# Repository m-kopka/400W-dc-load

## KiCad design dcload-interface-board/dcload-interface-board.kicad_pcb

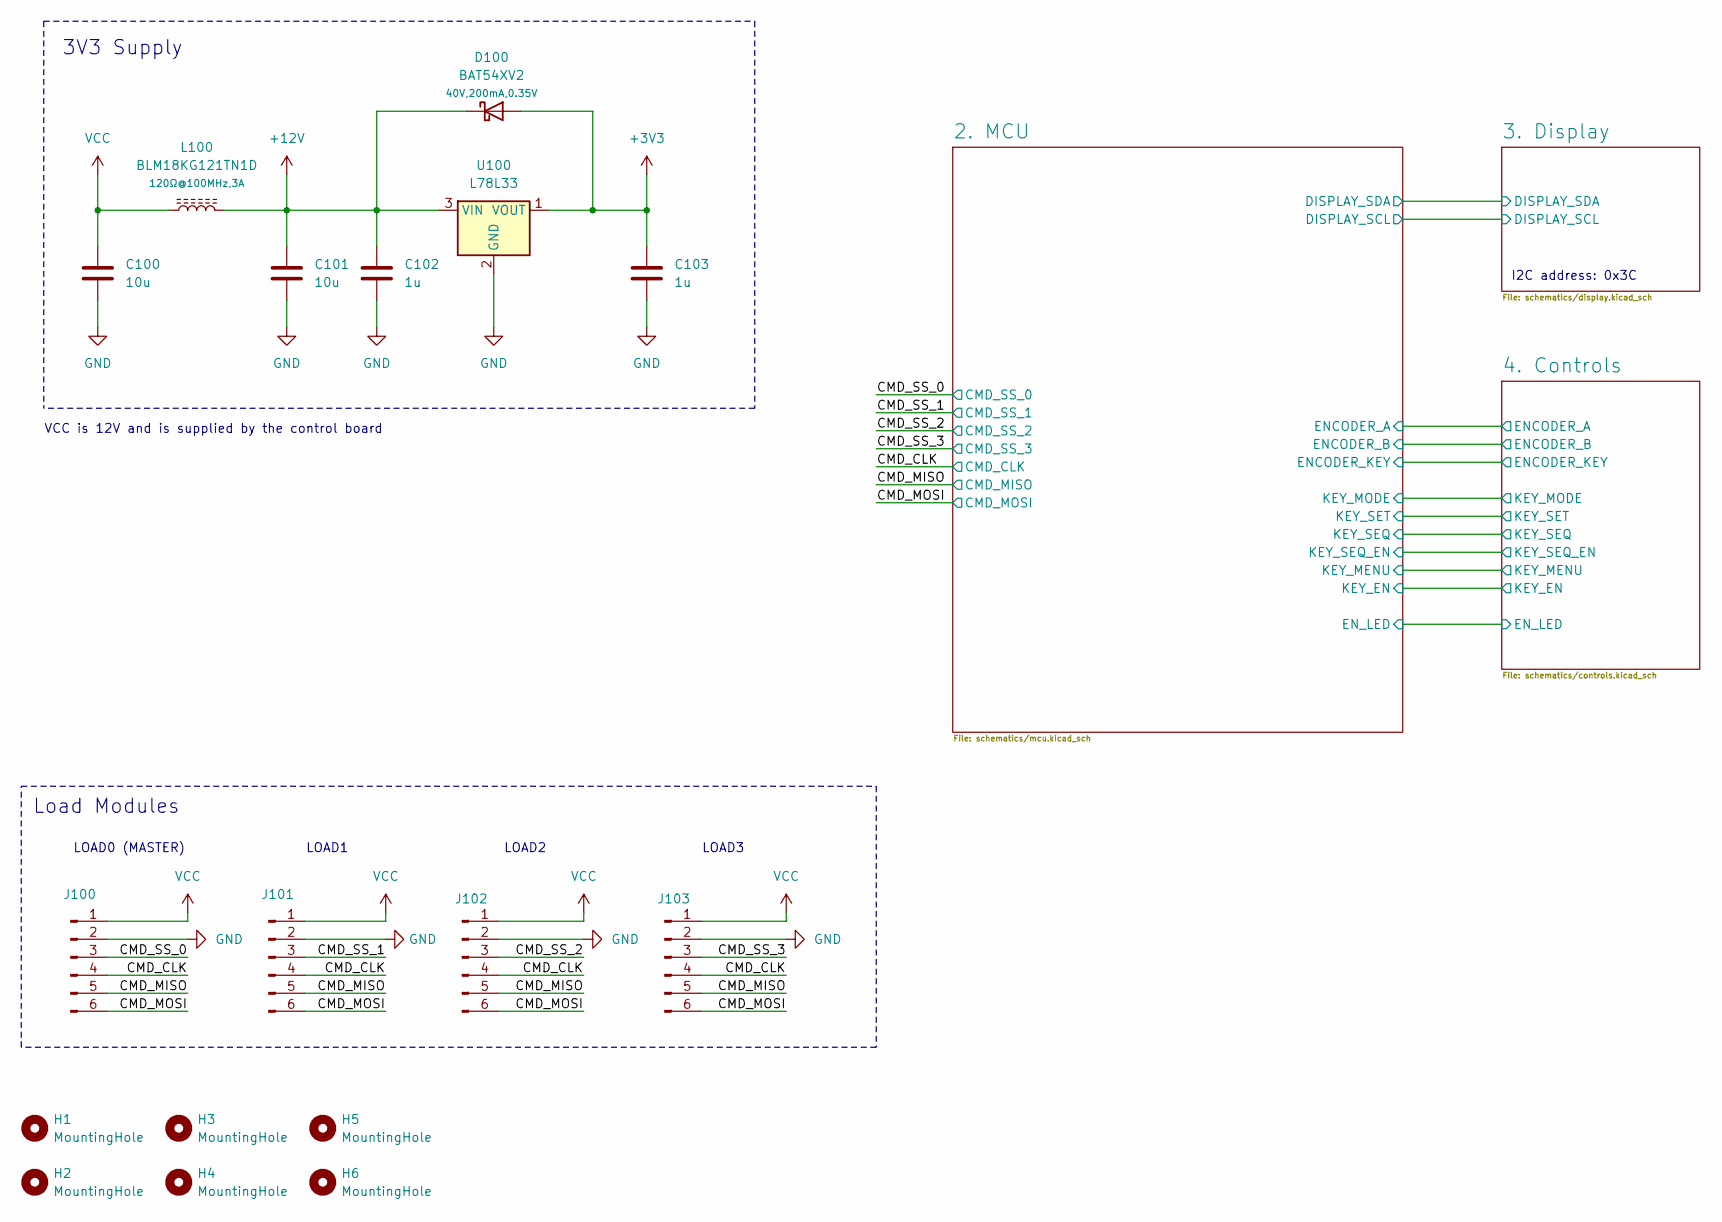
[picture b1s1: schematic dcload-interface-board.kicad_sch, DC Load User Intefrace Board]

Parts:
C100, C101: 10u; C_0603_1608Metric
C102, C103: 1u; C_0603_1608Metric
D100: BAT54XV2; SOD-523
H1, H2, H3, H4, H5, H6: MountingHole; MountingHole_3.2mm_M3
J100, J101, J102, J103: Conn_01x06_Male; PinHeader_1x06_P2.54mm_Vertical
L100: BLM18KG121TN1D; R_0603_1608Metric
U100: L78L33; SOT-89-3

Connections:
+3V3: C103.1, D100.2 (A), U100.1 (VOUT); also elsewhere on the board
+12V: C101.1, C102.1, D100.1 (K), L100.2, U100.3 (VIN)
/CMD_CLK: J100.4, J101.4, J102.4, J103.4; also elsewhere on the board
/CMD_MISO: J100.5, J101.5, J102.5, J103.5; also elsewhere on the board
/CMD_MOSI: J100.6, J101.6, J102.6, J103.6; also elsewhere on the board
/CMD_SS_0: J100.3; also elsewhere on the board
/CMD_SS_1: J101.3; also elsewhere on the board
/CMD_SS_2: J102.3; also elsewhere on the board
/CMD_SS_3: J103.3; also elsewhere on the board
GND: C100.2, C101.2, C102.2, C103.2, J100.2, J101.2, J102.2, J103.2, U100.2 (GND); also elsewhere on the board
VCC: C100.1, J100.1, J101.1, J102.1, J103.1, L100.1

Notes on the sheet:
Load Modules
LOAD1
VCC is 12V and is supplied by the control board
3V3 Supply
LOAD2
LOAD0 (MASTER)
I2C address: 0x3C
LOAD3

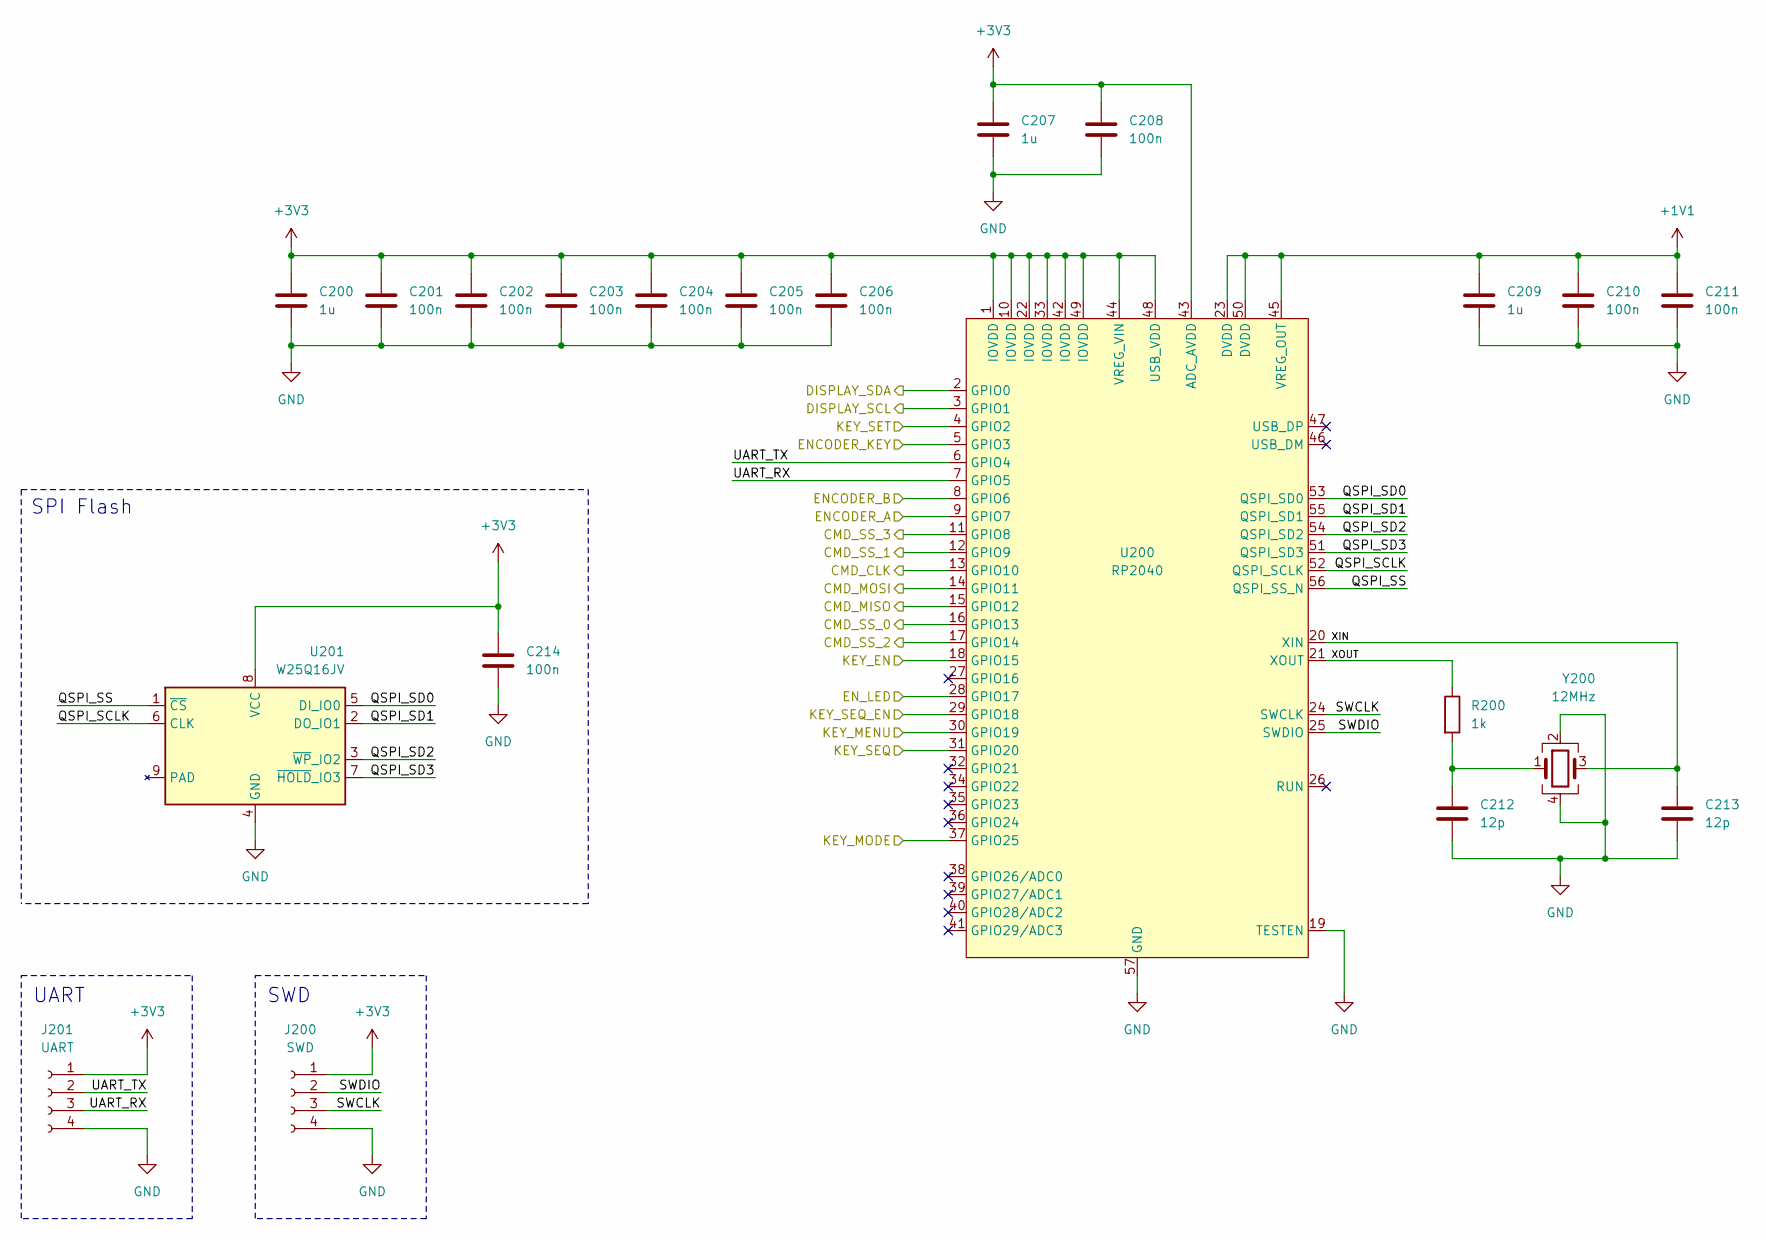
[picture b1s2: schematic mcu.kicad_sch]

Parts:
C200, C207, C209: 1u; C_0402_1005Metric
C201, C202, C203, C204, C205, C206, C208, C210, C211, C214: 100n; C_0402_1005Metric
C212, C213: 12p; C_0402_1005Metric
J200: SWD; PinHeader_1x04_P2.54mm_Vertical
J201: UART; PinHeader_1x04_P2.54mm_Vertical
R200: 1k; R_0402_1005Metric
U200: RP2040; QFN-56 7x7mm P0.4mm
U201: W25Q16JV; USON-8 2x3mm
Y200: 12MHz; Crystal 3225 3.2x2.5mm 4pin

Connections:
+1V1: C209.1, C210.1, C211.1, U200.23 (DVDD), U200.45 (VREG_OUT), U200.50 (DVDD)
+3V3: C200.1, C201.1, C202.1, C203.1, C204.1, C205.1, C206.1, C207.1, C208.1, C214.1, J200.1, J201.1, U200.1 (IOVDD), U200.10 (IOVDD), U200.22 (IOVDD), U200.33 (IOVDD), U200.42 (IOVDD), U200.43 (ADC_AVDD), U200.44 (VREG_VIN), U200.48 (USB_VDD), U200.49 (IOVDD), U201.8 (VCC); also elsewhere on the board
/2. MCU/DISPLAY_SCL: U200.3 (GPIO1); also elsewhere on the board
/2. MCU/DISPLAY_SDA: U200.2 (GPIO0); also elsewhere on the board
/2. MCU/ENCODER_A: U200.9 (GPIO7); also elsewhere on the board
/2. MCU/ENCODER_B: U200.8 (GPIO6); also elsewhere on the board
/2. MCU/ENCODER_KEY: U200.5 (GPIO3); also elsewhere on the board
/2. MCU/EN_LED: U200.28 (GPIO17); also elsewhere on the board
/2. MCU/KEY_EN: U200.18 (GPIO15); also elsewhere on the board
/2. MCU/KEY_MENU: U200.30 (GPIO19); also elsewhere on the board
/2. MCU/KEY_MODE: U200.37 (GPIO25); also elsewhere on the board
/2. MCU/KEY_SEQ: U200.31 (GPIO20); also elsewhere on the board
/2. MCU/KEY_SEQ_EN: U200.29 (GPIO18); also elsewhere on the board
/2. MCU/KEY_SET: U200.4 (GPIO2); also elsewhere on the board
/2. MCU/QSPI_SCLK: U200.52 (QSPI_SCLK), U201.6 (CLK)
/2. MCU/QSPI_SD0: U200.53 (QSPI_SD0), U201.5 (DI_IO0)
/2. MCU/QSPI_SD1: U200.55 (QSPI_SD1), U201.2 (DO_IO1)
/2. MCU/QSPI_SD2: U200.54 (QSPI_SD2), U201.3 (~WP_IO2)
/2. MCU/QSPI_SD3: U200.51 (QSPI_SD3), U201.7 (~HOLD_IO3)
/2. MCU/QSPI_SS: U200.56 (QSPI_SS_N), U201.1 (~CS)
/2. MCU/SWCLK: J200.3, U200.24 (SWCLK)
/2. MCU/SWDIO: J200.2, U200.25 (SWDIO)
/2. MCU/UART_RX: J201.3, U200.7 (GPIO5)
/2. MCU/UART_TX: J201.2, U200.6 (GPIO4)
/2. MCU/XIN: C213.1, U200.20 (XIN), Y200.3
/2. MCU/XOUT: R200.1, U200.21 (XOUT)
/CMD_CLK: U200.13 (GPIO10); also elsewhere on the board
/CMD_MISO: U200.15 (GPIO12); also elsewhere on the board
/CMD_MOSI: U200.14 (GPIO11); also elsewhere on the board
/CMD_SS_0: U200.16 (GPIO13); also elsewhere on the board
/CMD_SS_1: U200.12 (GPIO9); also elsewhere on the board
/CMD_SS_2: U200.17 (GPIO14); also elsewhere on the board
/CMD_SS_3: U200.11 (GPIO8); also elsewhere on the board
GND: C200.2, C201.2, C202.2, C203.2, C204.2, C205.2, C206.2, C207.2, C208.2, C209.2, C210.2, C211.2, C212.2, C213.2, C214.2, J200.4, J201.4, U200.19 (TESTEN), U200.57 (GND), U201.4 (GND), Y200.2, Y200.4; also elsewhere on the board
unnamed: C212.1, R200.2, Y200.1

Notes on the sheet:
UART
SWD
SPI Flash

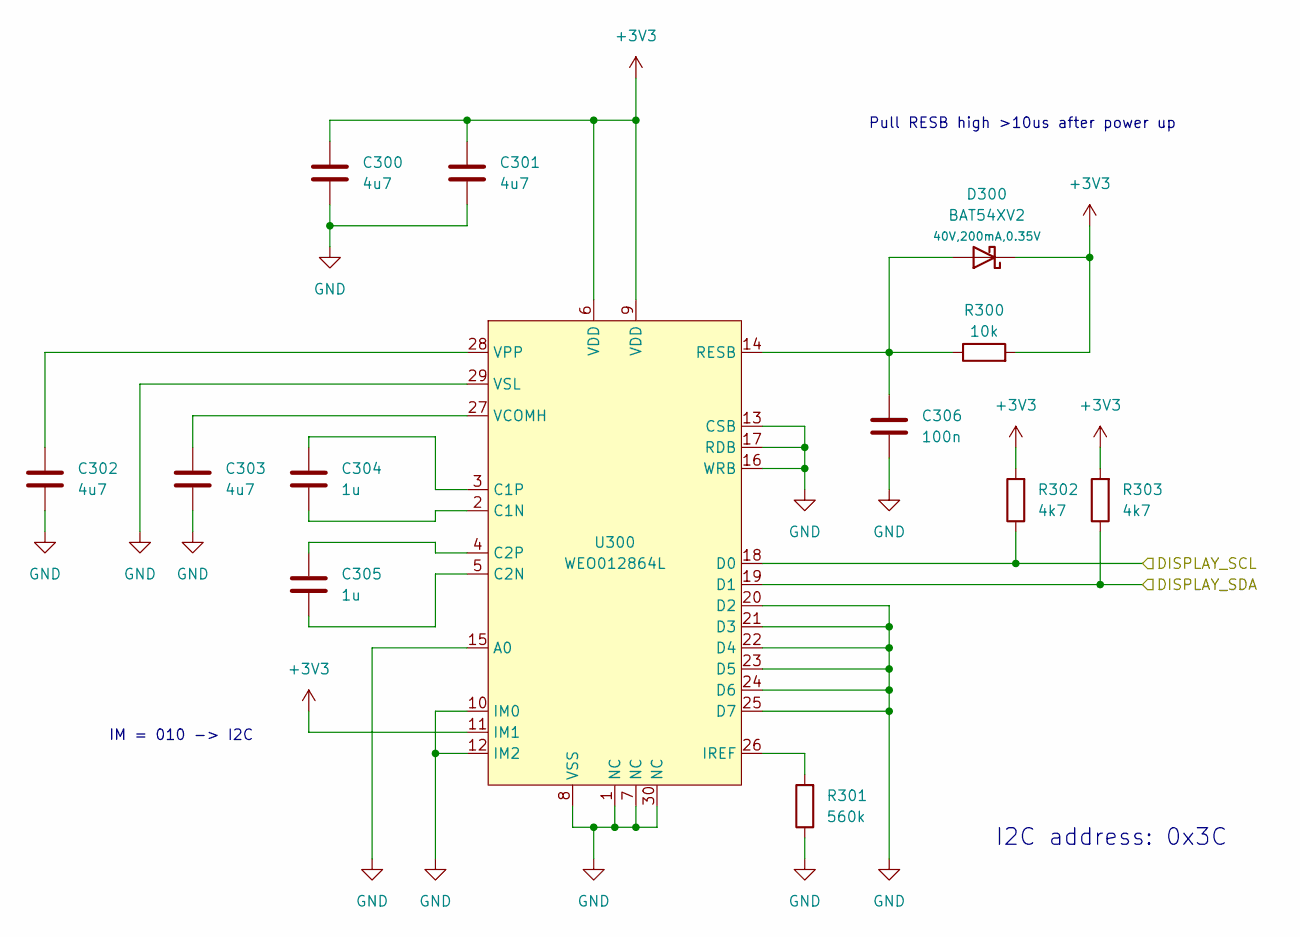
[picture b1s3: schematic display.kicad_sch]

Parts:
C300, C301, C302, C303: 4u7; C_0603_1608Metric
C304, C305: 1u; C_0402_1005Metric
C306: 100n; C_0402_1005Metric
D300: BAT54XV2; SOD-523
R300: 10k; R_0402_1005Metric
R301: 560k; R_0402_1005Metric
R302, R303: 4k7; R_0402_1005Metric
U300: WEO012864L

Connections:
+3V3: C300.1, C301.1, D300.1 (K), R300.2, R302.2, R303.2, U300.6 (VDD), U300.9 (VDD), U300.11 (IM1); also elsewhere on the board
/2. MCU/DISPLAY_SCL: R302.1, U300.18 (D0); also elsewhere on the board
/2. MCU/DISPLAY_SDA: R303.1, U300.19 (D1); also elsewhere on the board
GND: C300.2, C301.2, C302.2, C303.2, C306.2, R301.1, U300.1 (NC), U300.7 (NC), U300.8 (VSS), U300.10 (IM0), U300.12 (IM2), U300.13 (CSB), U300.15 (A0), U300.16 (WRB), U300.17 (RDB), U300.20 (D2), U300.21 (D3), U300.22 (D4), U300.23 (D5), U300.24 (D6), U300.25 (D7), U300.29 (VSL), U300.30 (NC); also elsewhere on the board
unnamed: C306.1, D300.2 (A), R300.1, U300.14 (RESB)
unnamed: C304.2, U300.2 (C1N)
unnamed: C304.1, U300.3 (C1P)
unnamed: C305.2, U300.5 (C2N)
unnamed: C305.1, U300.4 (C2P)
unnamed: R301.2, U300.26 (IREF)
unnamed: C303.1, U300.27 (VCOMH)
unnamed: C302.1, U300.28 (VPP)

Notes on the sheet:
IM = 010 -> I2C
Pull RESB high >10us after power up
I2C address: 0x3C

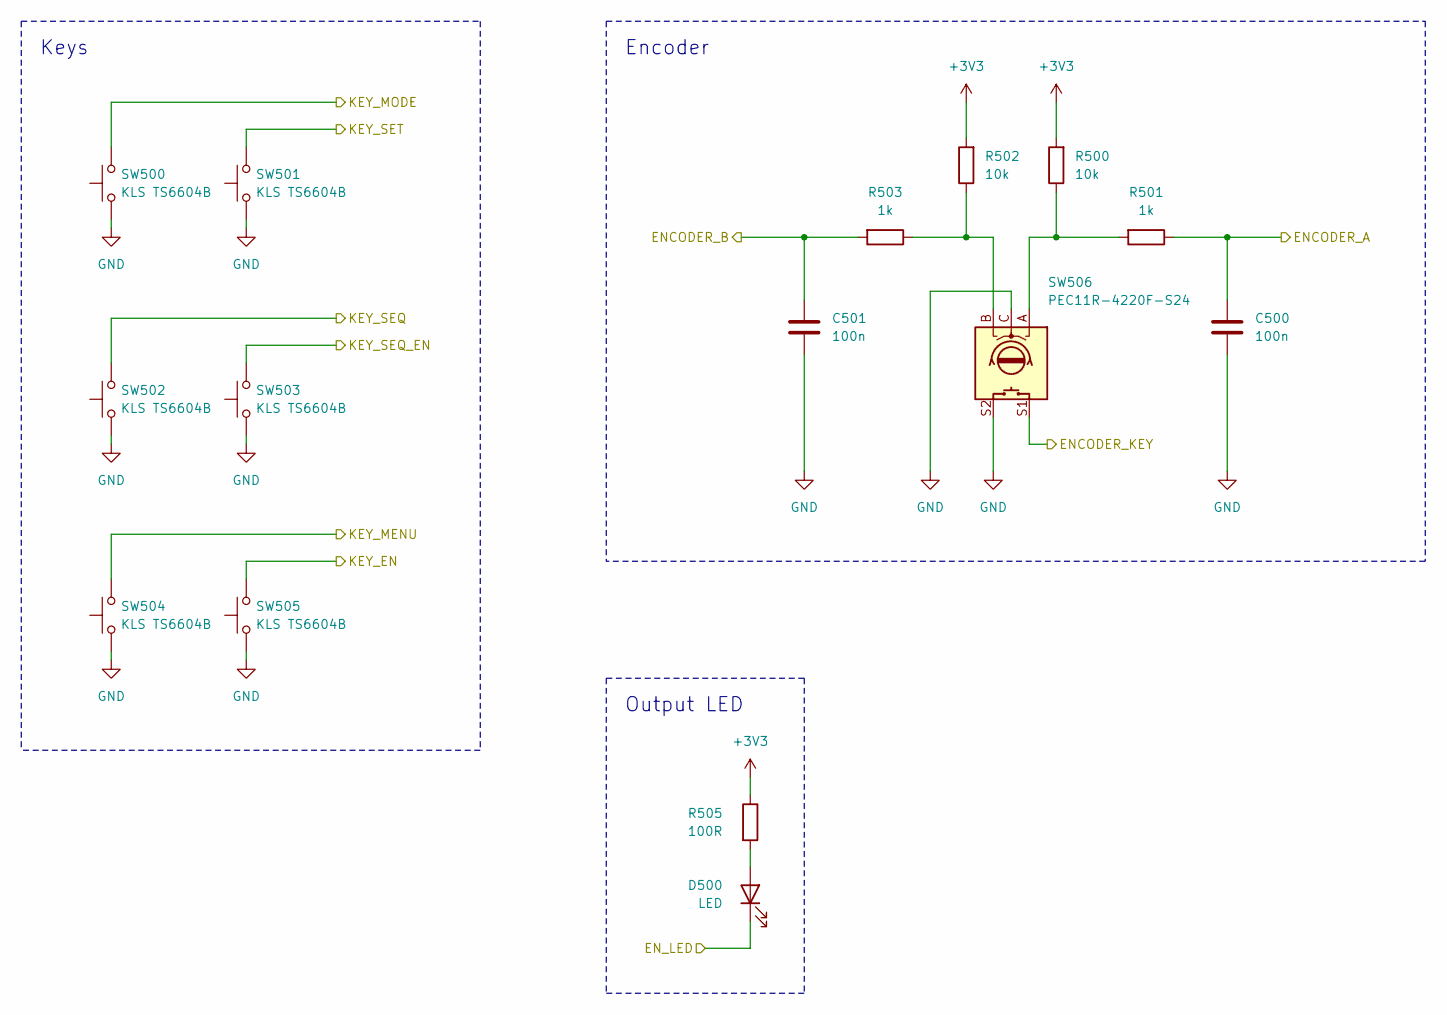
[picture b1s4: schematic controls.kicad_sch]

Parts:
C500, C501: 100n; C_0402_1005Metric
D500: LED; LED 0603
R500, R502: 10k; R_0402_1005Metric
R501, R503: 1k; R_0402_1005Metric
R505: 100R; R_0402_1005Metric
SW500, SW501, SW502, SW503, SW504, SW505: KLS TS6604B
SW506: PEC11R-4220F-S24; PEC11R-4220F-S0024

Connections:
+3V3: R500.2, R502.2, R505.1; also elsewhere on the board
/2. MCU/ENCODER_A: C500.1, R501.1; also elsewhere on the board
/2. MCU/ENCODER_B: C501.1, R503.2; also elsewhere on the board
/2. MCU/ENCODER_KEY: SW506.S1; also elsewhere on the board
/2. MCU/EN_LED: D500.1 (K); also elsewhere on the board
/2. MCU/KEY_EN: SW505.1; also elsewhere on the board
/2. MCU/KEY_MENU: SW504.1; also elsewhere on the board
/2. MCU/KEY_MODE: SW500.1; also elsewhere on the board
/2. MCU/KEY_SEQ: SW502.1; also elsewhere on the board
/2. MCU/KEY_SEQ_EN: SW503.1; also elsewhere on the board
/2. MCU/KEY_SET: SW501.1; also elsewhere on the board
GND: C500.2, C501.2, SW500.2, SW501.2, SW502.2, SW503.2, SW504.2, SW505.2, SW506.C, SW506.S2; also elsewhere on the board
unnamed: D500.2 (A), R505.2
unnamed: R500.1, R501.2, SW506.A
unnamed: R502.1, R503.1, SW506.B

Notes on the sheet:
Keys
Output LED
Encoder

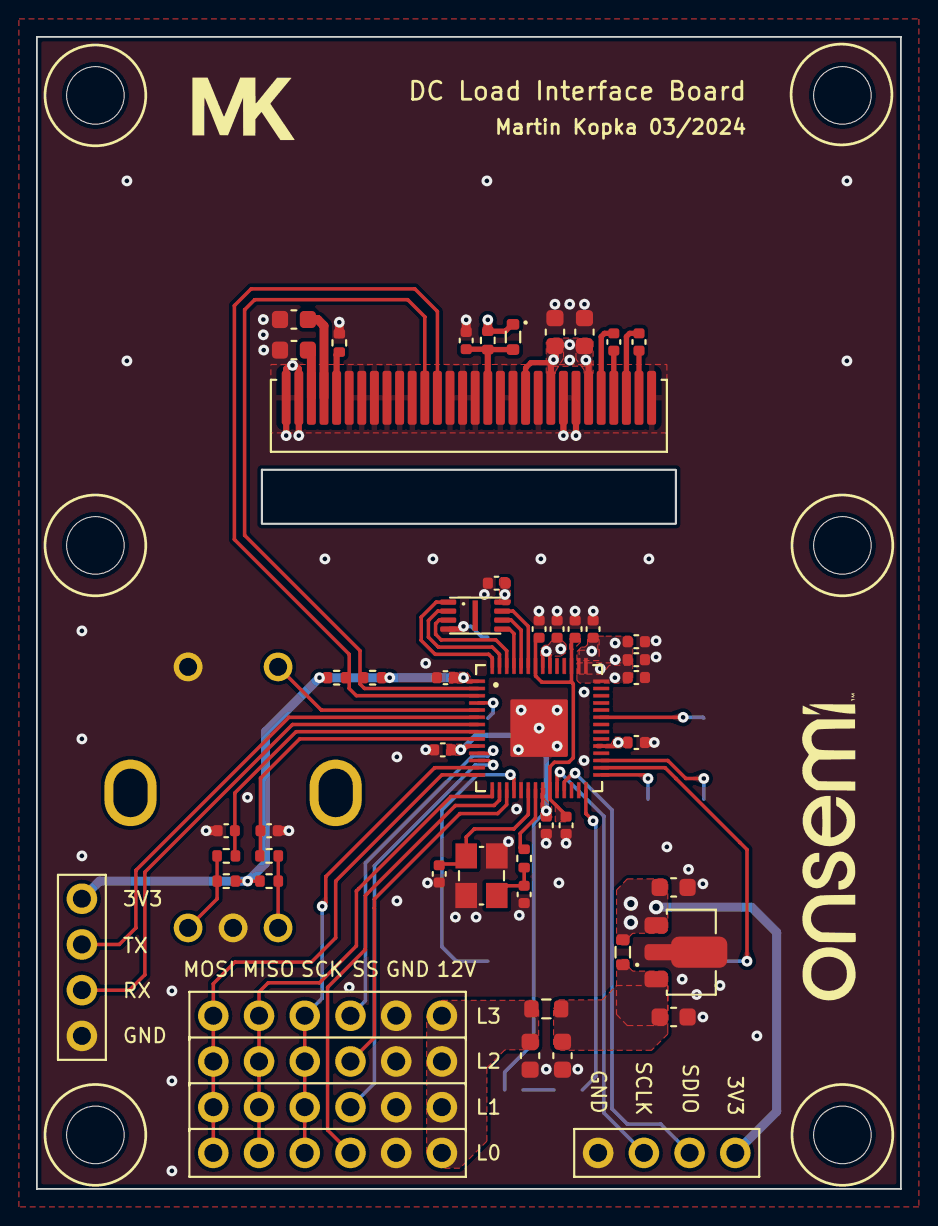
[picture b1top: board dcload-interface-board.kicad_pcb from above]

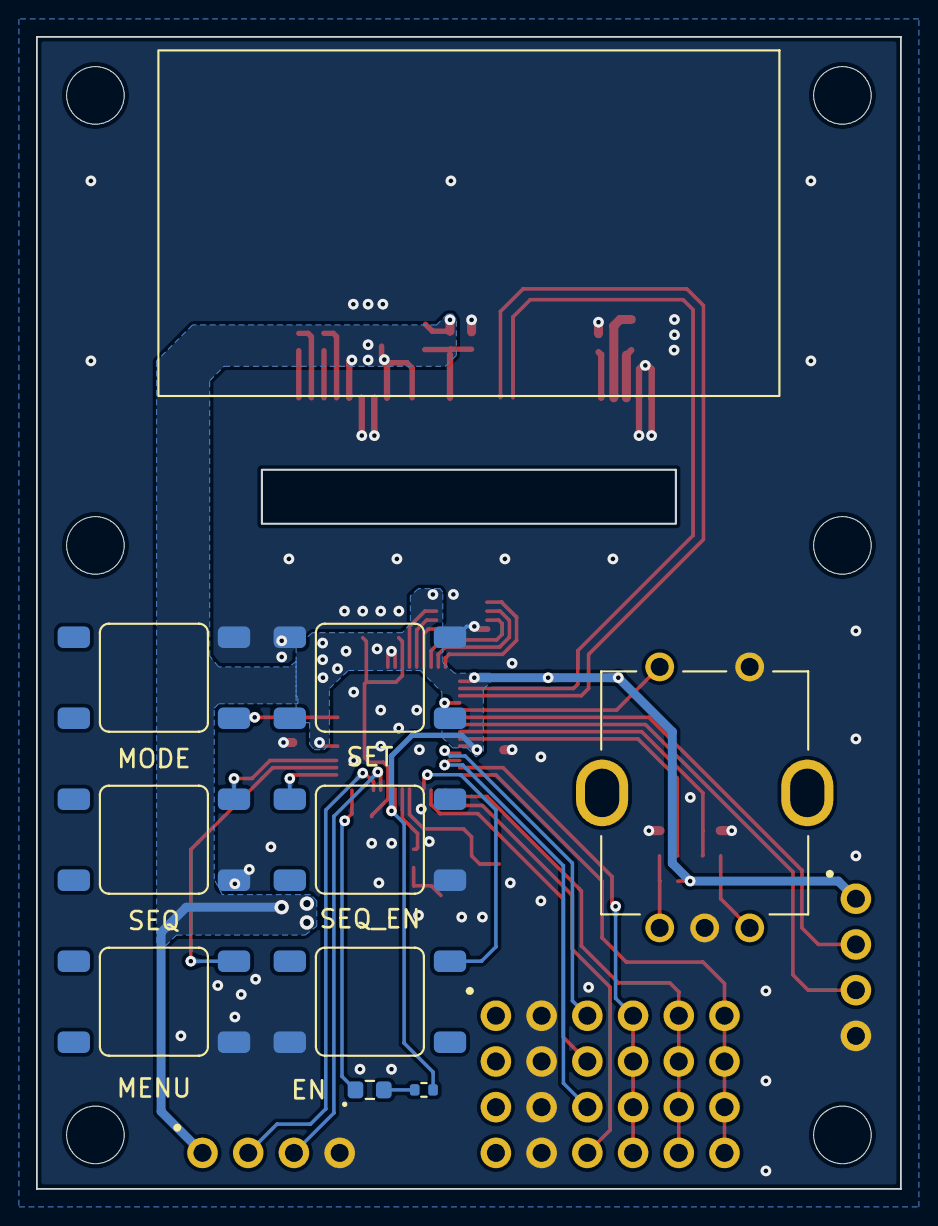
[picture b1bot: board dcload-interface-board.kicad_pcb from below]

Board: 2 copper layers, 48.0 x 64.0 mm, 66 parts (9 on the bottom side), 48 nets.

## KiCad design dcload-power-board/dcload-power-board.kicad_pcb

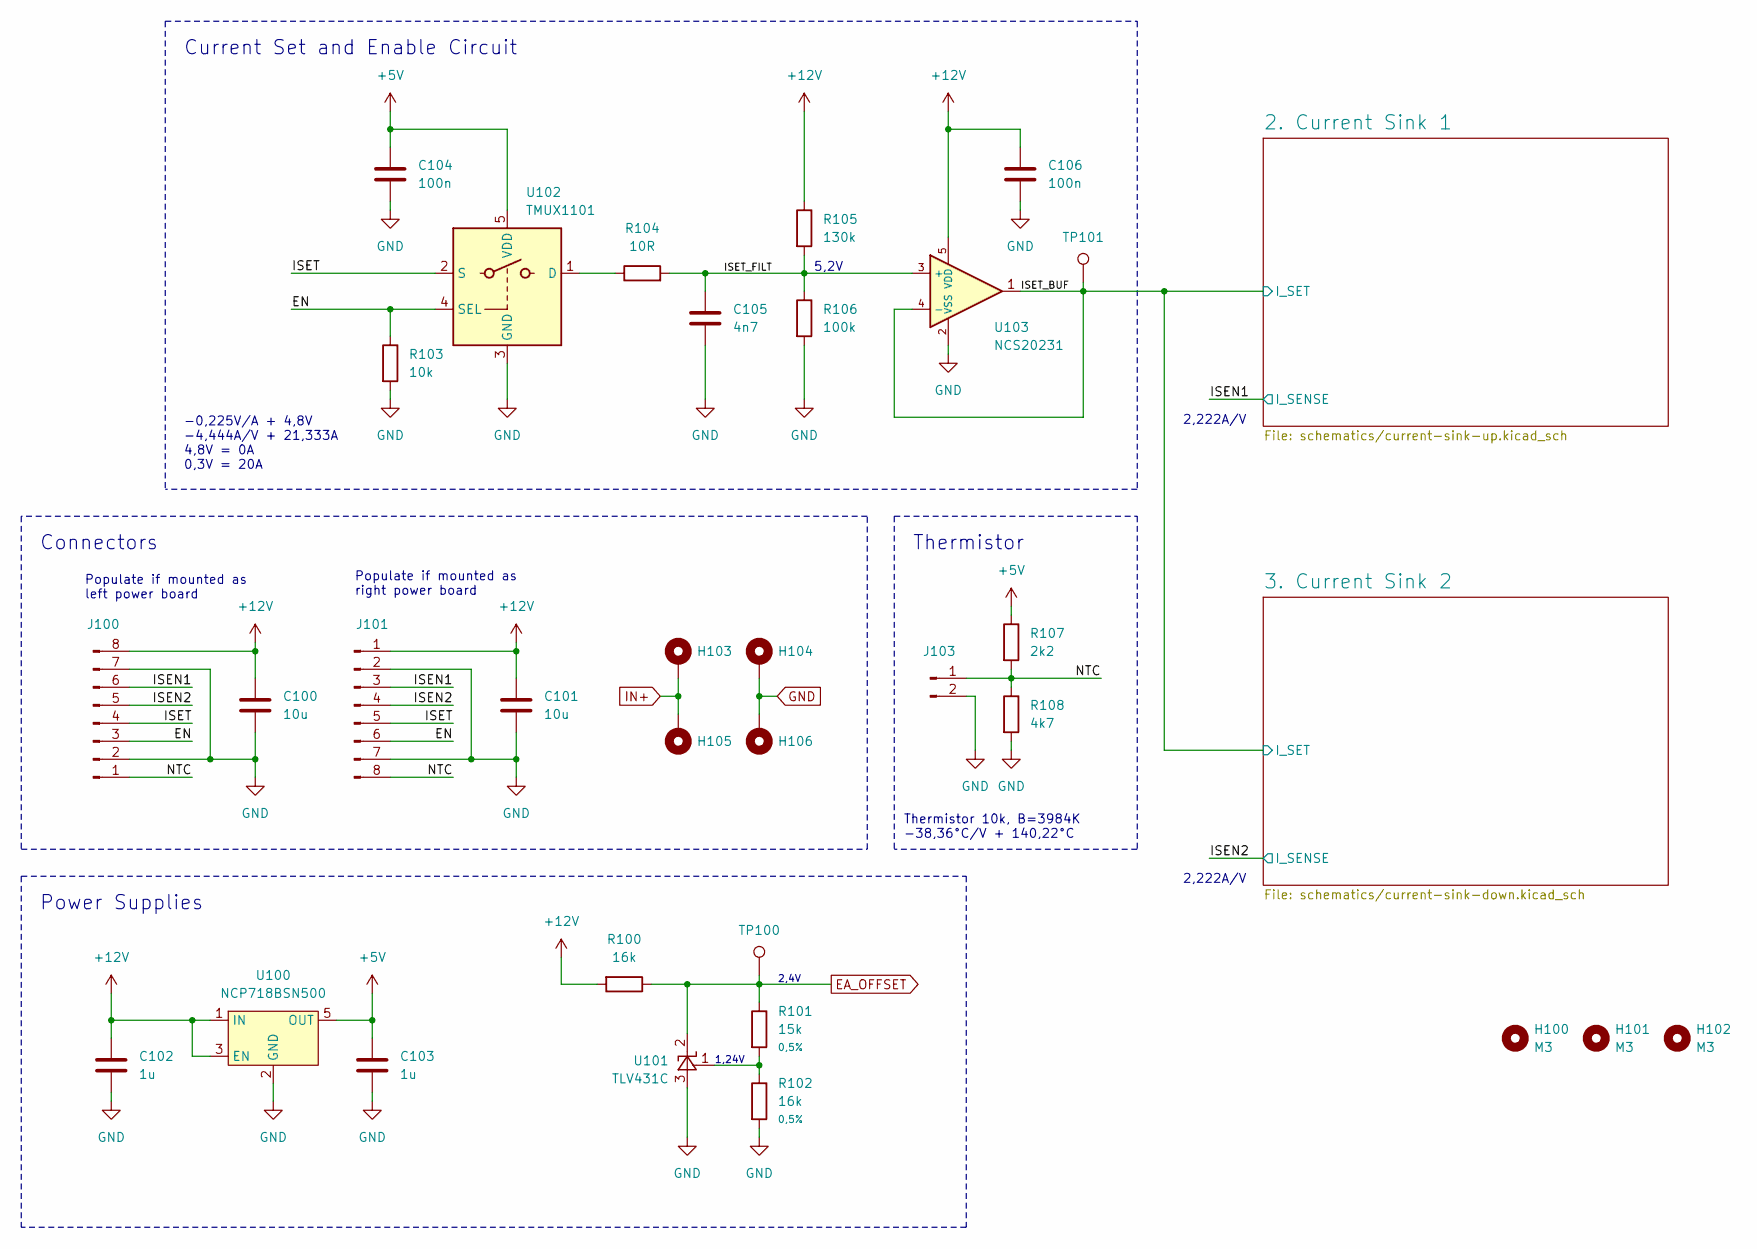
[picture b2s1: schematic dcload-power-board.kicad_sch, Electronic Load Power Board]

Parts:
C100, C101: 10u; C_1206_3216Metric
C102, C103: 1u; C_0603_1608Metric
C104, C106: 100n; C_0603_1608Metric
C105: 4n7; C_0603_1608Metric
H100, H101, H102: M3; MountingHole_3.2mm_M3
H103, H104, H105, H106: MountingHole_Pad; MountingHole_3.2mm_M3_DIN965_Pad
J100, J101: Conn_01x08_Male; PinHeader_1x08_P2.54mm_Horizontal
J103: Conn_01x02_Male; PinHeader_1x02_P2.54mm_Horizontal
R100: 16k; R_0603_1608Metric
R101: 15k; R_0603_1608Metric; Tolerance 0,5%
R102: 16k; R_0603_1608Metric; Tolerance 0,5%
R103: 10k; R_0603_1608Metric
R104: 10R; R_0603_1608Metric
R105: 130k; R_0603_1608Metric
R106: 100k; R_0603_1608Metric
R107: 2k2; R_0603_1608Metric
R108: 4k7; R_0603_1608Metric
TP100, TP101: TestPoint; TestPoint_Pad_D1.0mm
U100: NCP718BSN500; SOT-23-5L
U101: TLV431C; SOT-23
U102: TMUX1101; SOT-23-5L
U103: NCS20231; SOT-23-5L

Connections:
+5V: C103.2, C104.2, R107.1, U100.5 (OUT), U102.5 (VDD); also elsewhere on the board
+12V: C100.2, C101.2, C102.2, C106.2, J100.8, J101.1, R100.2, R105.1, U100.1 (IN), U100.3 (EN), U103.5 (VDD); also elsewhere on the board
/EN: J100.3, J101.6, R103.1, U102.4 (SEL)
/ISEN1: J100.6, J101.3; also elsewhere on the board
/ISEN2: J100.5, J101.4; also elsewhere on the board
/ISET: J100.4, J101.5, U102.2 (S)
/ISET_BUF: TP101.1, U103.1, U103.4 (-); also elsewhere on the board
/ISET_FILT: C105.2, R104.2, R105.2, R106.1, U103.3 (+)
/NTC: J100.1, J101.8, J103.1, R107.2, R108.1
EA_OFFSET: R100.1, R101.1, TP100.1, U101.2 (K); also elsewhere on the board
GND: C100.1, C101.1, C102.1, C103.1, C104.1, C105.1, C106.1, H104.1, H106.1, J100.2, J100.7, J101.2, J101.7, J103.2, R102.2, R103.2, R106.2, R108.2, U100.2 (GND), U101.3 (A), U102.3 (GND), U103.2 (VSS); also elsewhere on the board
IN+: H103.1, H105.1; also elsewhere on the board
unnamed: R101.2, R102.1, U101.1 (REF)
unnamed: R104.1, U102.1 (D)

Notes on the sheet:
Connectors
Populate if mounted as right power board
2,222A/V
Thermistor 10k, B=3984K -38,36°C/V + 140,22°C
1,24V
Power Supplies
Populate if mounted as left power board
Thermistor
5,2V
-0,225V/A + 4,8V -4,444A/V + 21,333A 4,8V = 0A 0,3V = 20A
2,4V
Current Set and Enable Circuit

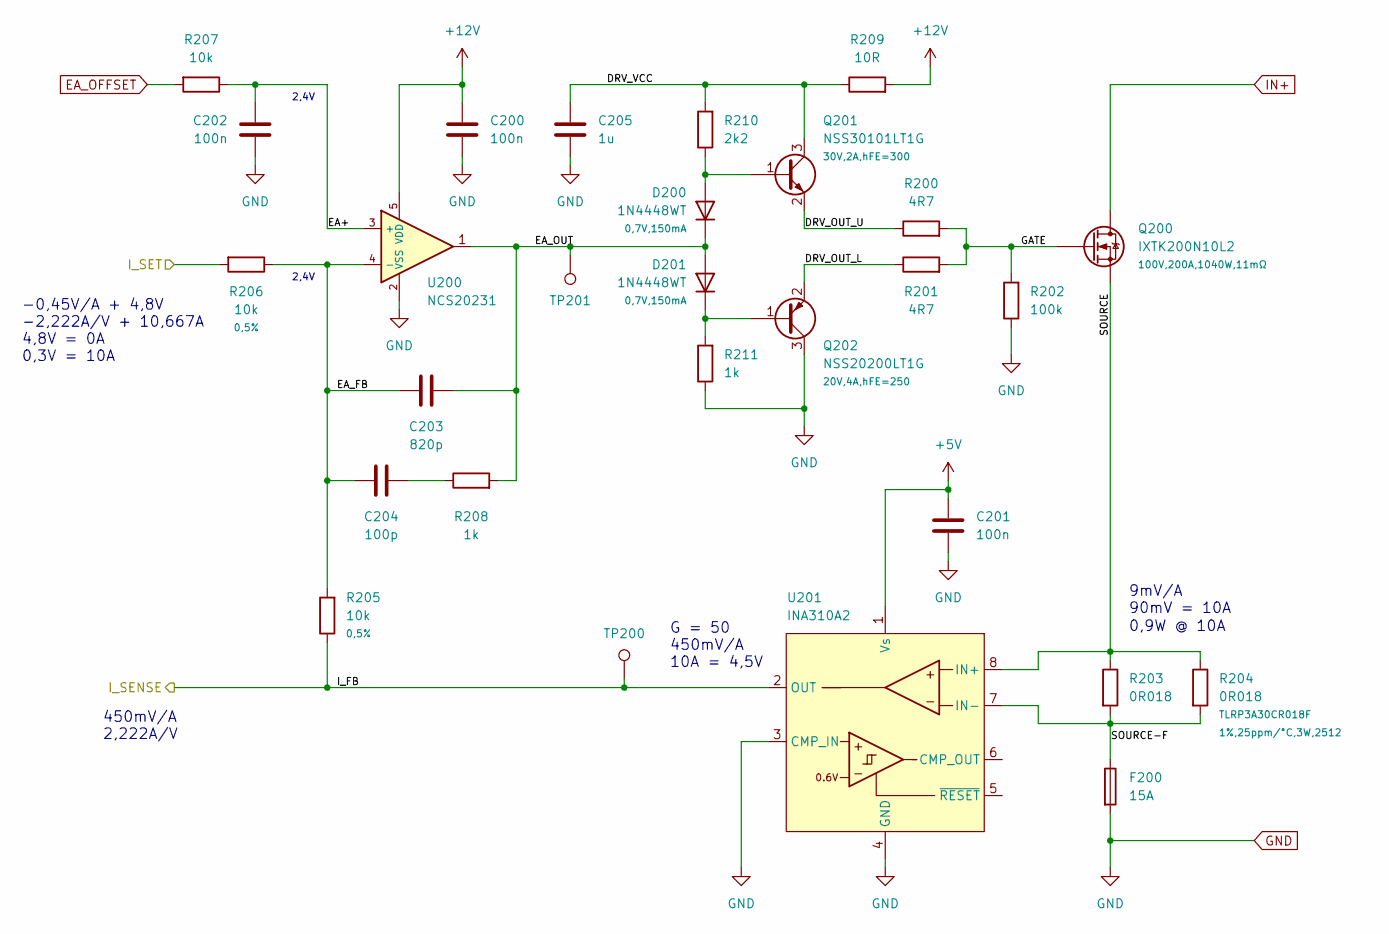
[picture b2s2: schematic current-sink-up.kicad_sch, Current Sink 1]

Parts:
C200, C201, C202: 100n; C_0603_1608Metric
C203: 820p; C_0603_1608Metric
C204: 100p; C_0603_1608Metric
C205: 1u; C_0603_1608Metric
D200, D201: 1N4448WT; SOD-523
F200: 15A; 2410
Q200: IXTK200N10L2; TO264
Q201: NSS30101LT1G; SOT-23
Q202: NSS20200LT1G; SOT-23
R200, R201: 4R7; R_0603_1608Metric
R202: 100k; R_0603_1608Metric
R203, R204: 0R018; R_2512_6332Metric
R205, R206: 10k; R_0603_1608Metric; Tolerance 0,5%
R207: 10k; R_0603_1608Metric
R208, R211: 1k; R_0603_1608Metric
R209: 10R; R_0603_1608Metric
R210: 2k2; R_0603_1608Metric
TP200, TP201: TestPoint; TestPoint_Pad_D1.0mm
U200: NCS20231; SOT-23-5L
U201: INA310A2; VSSOP-8_3x3mm_P0.65mm

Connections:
+5V: C201.2, U201.1 (Vs); also elsewhere on the board
+12V: C200.2, R209.2, U200.5 (VDD); also elsewhere on the board
/2. Current Sink 1/DRV_OUT_L: Q202.2 (E), R201.1
/2. Current Sink 1/DRV_OUT_U: Q201.2 (E), R200.1
/2. Current Sink 1/DRV_VCC: C205.2, Q201.3 (C), R209.1, R210.2
/2. Current Sink 1/EA+: C202.2, R207.1, U200.3 (+)
/2. Current Sink 1/EA_FB: C203.1, C204.1, R205.2, R206.1, U200.4 (-)
/2. Current Sink 1/EA_OUT: C203.2, D200.1 (K), D201.2 (A), R208.2, TP201.1, U200.1
/2. Current Sink 1/GATE: Q200.1 (G), R200.2, R201.2, R202.2
/2. Current Sink 1/SOURCE: Q200.3 (S), R203.1, R204.1, U201.8 (IN+)
/2. Current Sink 1/SOURCE-F: F200.1, R203.2, R204.2, U201.7 (IN-)
/ISEN1: R205.1, TP200.1, U201.2 (OUT); also elsewhere on the board
/ISET_BUF: R206.2; also elsewhere on the board
EA_OFFSET: R207.2; also elsewhere on the board
GND: C200.1, C201.1, C202.1, C205.1, F200.2, Q202.3 (C), R202.1, R211.1, U200.2 (VSS), U201.3 (CMP_IN), U201.4 (GND); also elsewhere on the board
IN+: Q200.2 (D); also elsewhere on the board
unnamed: C204.2, R208.1
unnamed: D200.2 (A), Q201.1 (B), R210.1
unnamed: D201.1 (K), Q202.1 (B), R211.2

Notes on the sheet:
0,9W @ 10A
-0,45V/A + 4,8V -2,222A/V + 10,667A 4,8V = 0A 0,3V = 10A
2,4V
450mV/A 2,222A/V
9mV/A 90mV = 10A
G = 50 450mV/A 10A = 4,5V

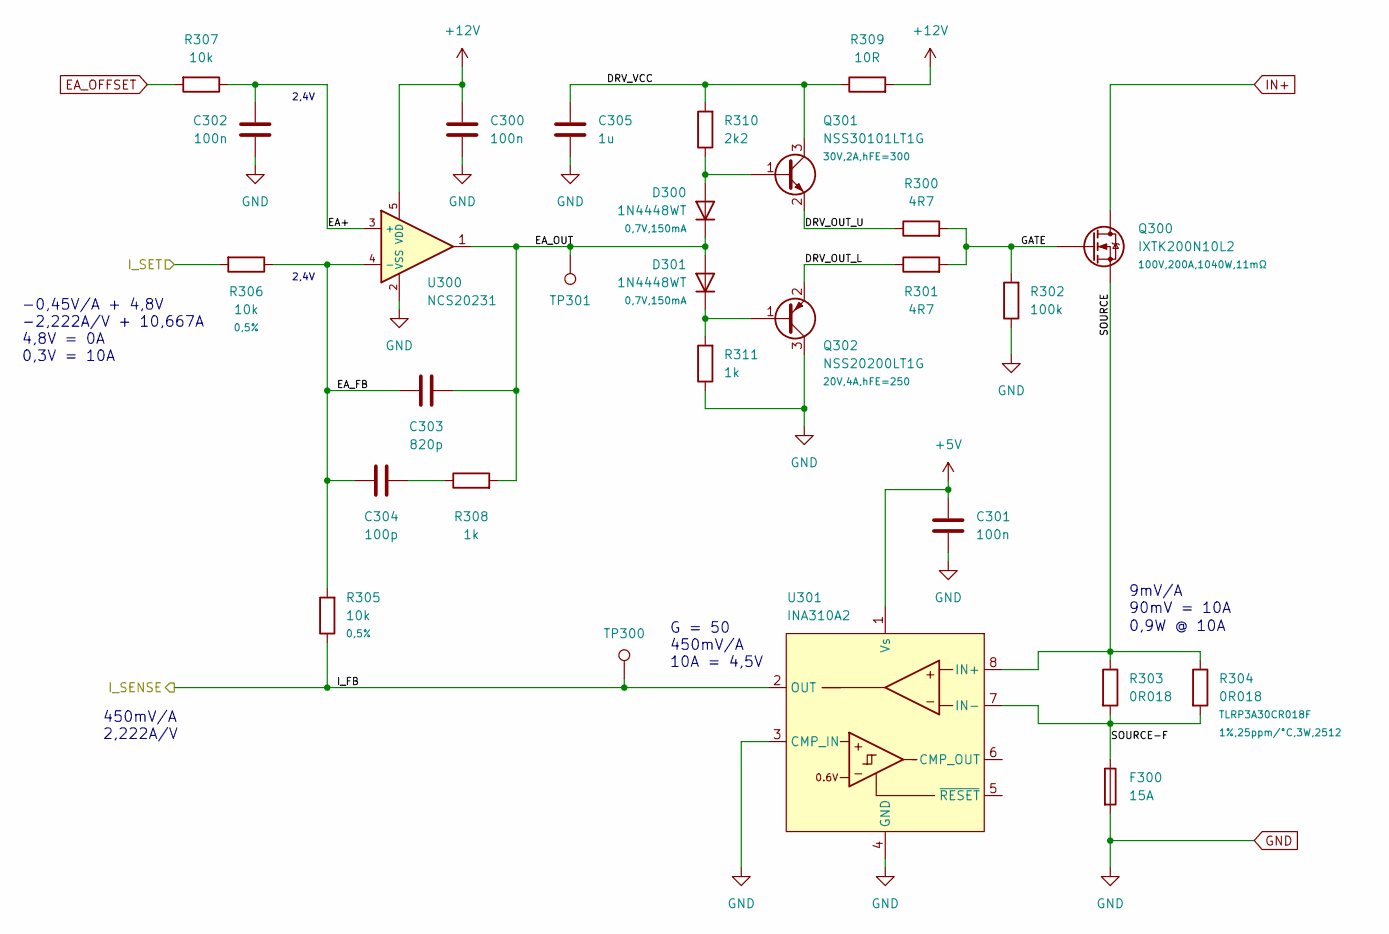
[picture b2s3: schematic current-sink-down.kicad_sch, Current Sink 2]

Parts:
C300, C301, C302: 100n; C_0603_1608Metric
C303: 820p; C_0603_1608Metric
C304: 100p; C_0603_1608Metric
C305: 1u; C_0603_1608Metric
D300, D301: 1N4448WT; SOD-523
F300: 15A; 2410
Q300: IXTK200N10L2; TO264
Q301: NSS30101LT1G; SOT-23
Q302: NSS20200LT1G; SOT-23
R300, R301: 4R7; R_0603_1608Metric
R302: 100k; R_0603_1608Metric
R303, R304: 0R018; R_2512_6332Metric
R305, R306: 10k; R_0603_1608Metric; Tolerance 0,5%
R307: 10k; R_0603_1608Metric
R308, R311: 1k; R_0603_1608Metric
R309: 10R; R_0603_1608Metric
R310: 2k2; R_0603_1608Metric
TP300, TP301: TestPoint; TestPoint_Pad_D1.0mm
U300: NCS20231; SOT-23-5L
U301: INA310A2; VSSOP-8_3x3mm_P0.65mm

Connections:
+5V: C301.2, U301.1 (Vs); also elsewhere on the board
+12V: C300.2, R309.2, U300.5 (VDD); also elsewhere on the board
/3. Current Sink 2/DRV_OUT_L: Q302.2 (E), R301.1
/3. Current Sink 2/DRV_OUT_U: Q301.2 (E), R300.1
/3. Current Sink 2/DRV_VCC: C305.2, Q301.3 (C), R309.1, R310.2
/3. Current Sink 2/EA+: C302.2, R307.1, U300.3 (+)
/3. Current Sink 2/EA_FB: C303.1, C304.1, R305.2, R306.1, U300.4 (-)
/3. Current Sink 2/EA_OUT: C303.2, D300.1 (K), D301.2 (A), R308.2, TP301.1, U300.1
/3. Current Sink 2/GATE: Q300.1 (G), R300.2, R301.2, R302.2
/3. Current Sink 2/SOURCE: Q300.3 (S), R303.1, R304.1, U301.8 (IN+)
/3. Current Sink 2/SOURCE-F: F300.1, R303.2, R304.2, U301.7 (IN-)
/ISEN2: R305.1, TP300.1, U301.2 (OUT); also elsewhere on the board
/ISET_BUF: R306.2; also elsewhere on the board
EA_OFFSET: R307.2; also elsewhere on the board
GND: C300.1, C301.1, C302.1, C305.1, F300.2, Q302.3 (C), R302.1, R311.1, U300.2 (VSS), U301.3 (CMP_IN), U301.4 (GND); also elsewhere on the board
IN+: Q300.2 (D); also elsewhere on the board
unnamed: C304.2, R308.1
unnamed: D300.2 (A), Q301.1 (B), R310.1
unnamed: D301.1 (K), Q302.1 (B), R311.2

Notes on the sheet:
0,9W @ 10A
450mV/A 2,222A/V
2,4V
G = 50 450mV/A 10A = 4,5V
-0,45V/A + 4,8V -2,222A/V + 10,667A 4,8V = 0A 0,3V = 10A
9mV/A 90mV = 10A
